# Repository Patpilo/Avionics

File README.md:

# Avionics
Avionics for Lynx Rocket

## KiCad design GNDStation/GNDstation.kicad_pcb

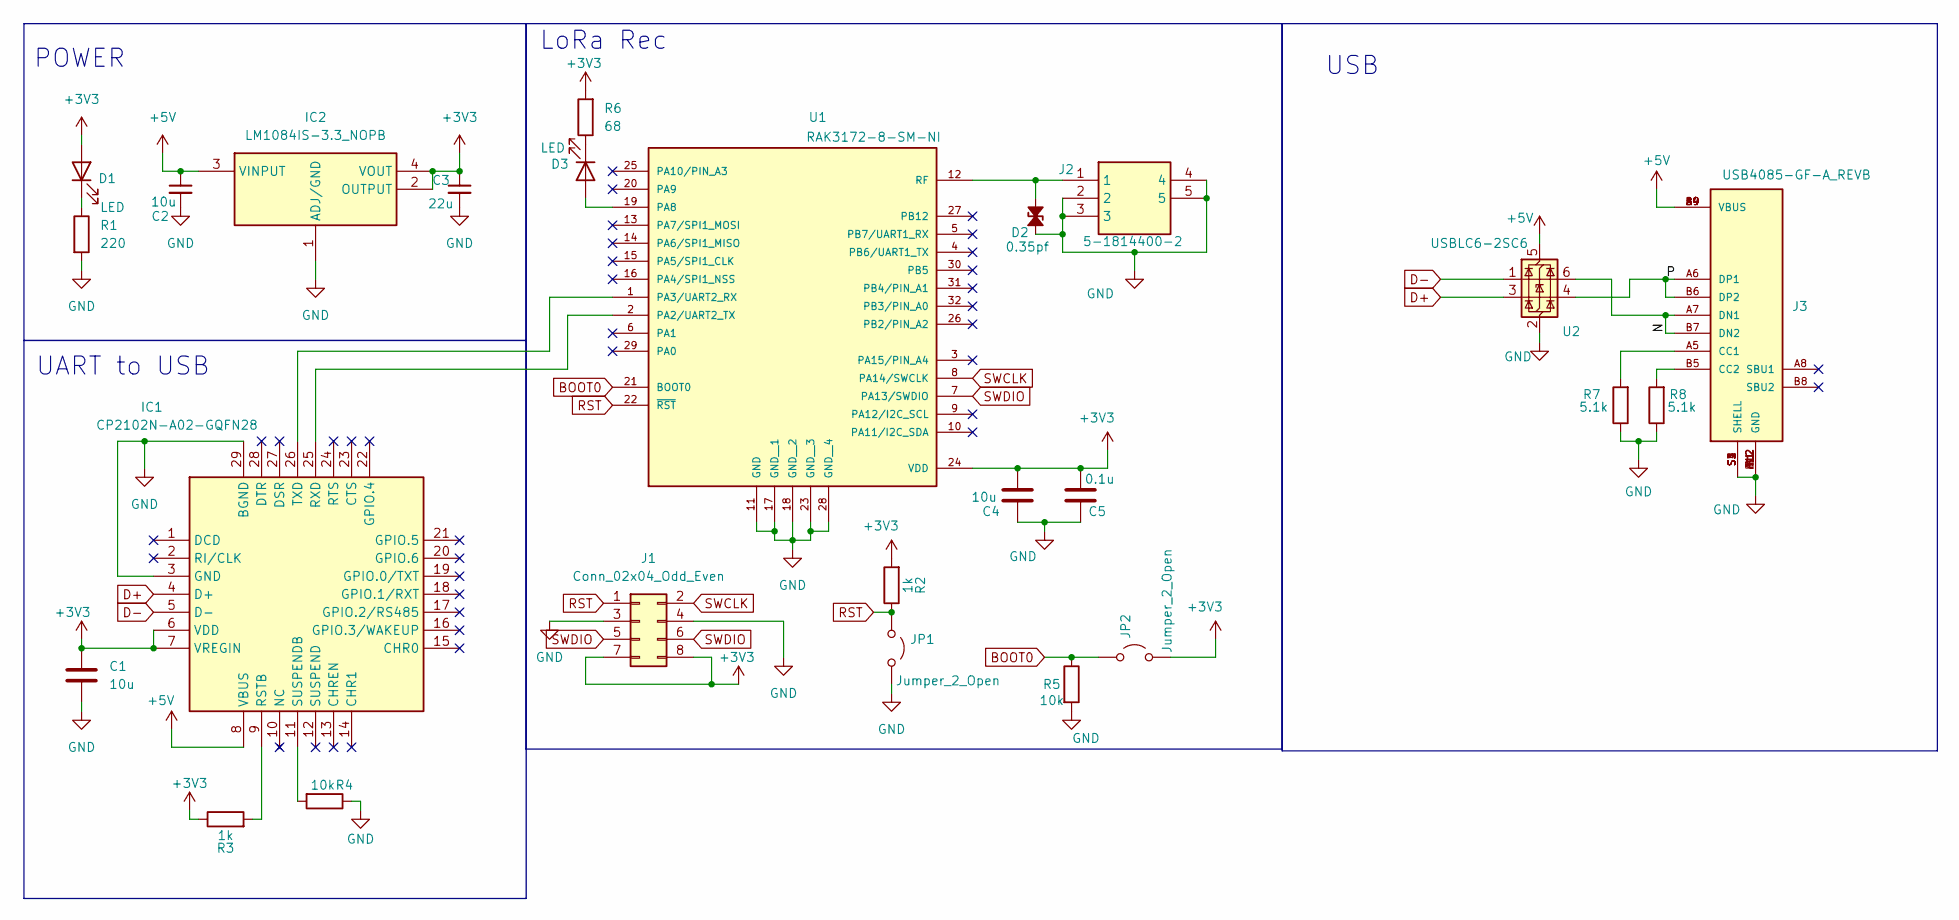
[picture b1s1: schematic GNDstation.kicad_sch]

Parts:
C1, C2, C4: 10u; C_0805_2012Metric_Pad1.18x1.45mm_HandSolder
C3: 22u; C_0805_2012Metric_Pad1.18x1.45mm_HandSolder
C5: 0.1u; C_0201_0603Metric_Pad0.64x0.40mm_HandSolder
D1, D3: LED; LED_0805_2012Metric_Pad1.15x1.40mm_HandSolder
D2: 0.35pf; D_01005_0402Metric_Pad0.57x0.30mm_HandSolder
IC1: CP2102N-A02-GQFN28; QFN50P500X500X80-29N-D; Manufacturer_Part_Number CP2102N-A02-GQFN28; Mouser Part Number 634-CP2102NA02GQFN28
IC2: LM1084IS-3.3_NOPB; TO254P1435X464-4N; Manufacturer_Part_Number LM1084IS-3.3/NOPB; Mouser Part Number 926-LM1084IS-3.3NOPB
J1: Conn_02x04_Odd_Even; PinHeader_2x04_P2.54mm_Vertical
J2: 5-1814400-2; 518144002; Manufacturer_Part_Number 5-1814400-2; Mouser Part Number 571-5-1814400-2
J3: USB4085-GF-A_REVB; GCT_USB4085-GF-A_REVB; PARTREV B
JP1, JP2: Jumper_2_Open; SolderJumper-2_P1.3mm_Open_RoundedPad1.0x1.5mm
R1: 220; R_0805_2012Metric_Pad1.20x1.40mm_HandSolder
R2, R3: 1k; R_0402_1005Metric_Pad0.72x0.64mm_HandSolder
R4, R5: 10k; R_0805_2012Metric_Pad1.20x1.40mm_HandSolder
R6: 68; R_0805_2012Metric_Pad1.20x1.40mm_HandSolder
R7, R8: 5.1k; R_0402_1005Metric_Pad0.72x0.64mm_HandSolder
U1: RAK3172-8-SM-NI; XCVR_RAK3172-8-SM-NI; PARTREV 4/11/2023
U2: USBLC6-2SC6; SOT-23-6

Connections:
+3V3: C1.1, C3.1, C4.2, C5.2, D1.2 (A), IC1.6 (VDD), IC1.7 (VREGIN), IC2.2 (OUTPUT), IC2.4 (VOUT), J1.7, J1.8, JP2.2 (B), R2.2, R3.1, R6.2, U1.24 (VDD)
+5V: C2.1, IC1.8 (VBUS), IC2.3 (VINPUT), J3.A4 (VBUS), J3.A9 (VBUS), J3.B4 (VBUS), J3.B9 (VBUS), U2.5 (VBUS)
/N: J3.A7 (DN1), J3.B7 (DN2), U2.6 (I/O1)
/P: J3.A6 (DP1), J3.B6 (DP2), U2.4 (I/O2)
BOOT0: JP2.1 (A), R5.1, U1.21 (BOOT0)
D+: IC1.4 (D+), U2.3 (I/O2)
D-: IC1.5 (D-), U2.1 (I/O1)
GND: C1.2, C2.2, C3.2, C4.1, C5.1, D2.1 (A1), IC1.3 (GND), IC1.29 (BGND), IC2.1 (ADJ/GND), J1.3, J1.4, J2.2, J2.3, J2.4, J2.5, J3.A1 (GND), J3.A12 (GND), J3.B1 (GND), J3.B12 (GND), J3.S1 (SHELL), J3.S2 (SHELL), J3.S3 (SHELL), J3.S4 (SHELL), JP1.2 (B), R1.2, R4.1, R5.2, R7.1, R8.1, U1.11 (GND), U1.17 (GND__1), U1.18 (GND__2), U1.23 (GND__3), U1.28 (GND__4), U2.2 (GND)
unnamed: D1.1 (K), R1.1
unnamed: D2.2 (A2), J2.1, U1.12 (RF)
unnamed: D3.2 (A), U1.19 (PA8)
unnamed: D3.1 (K), R6.1
unnamed: IC1.9 (RSTB), R3.2
unnamed: IC1.25 (RXD), U1.2 (PA2/UART2_TX)
unnamed: IC1.11 (SUSPENDB), R4.2
unnamed: IC1.26 (TXD), U1.1 (PA3/UART2_RX)
unnamed: J3.A5 (CC1), R7.2
unnamed: J3.B5 (CC2), R8.2
RST: J1.1, JP1.1 (A), R2.1, U1.22 (~RST)
SWCLK: J1.2, U1.8 (PA14/SWCLK)
SWDIO: J1.5, J1.6, U1.7 (PA13/SWDIO)

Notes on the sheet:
POWER
UART to USB
LoRa Rec
USB

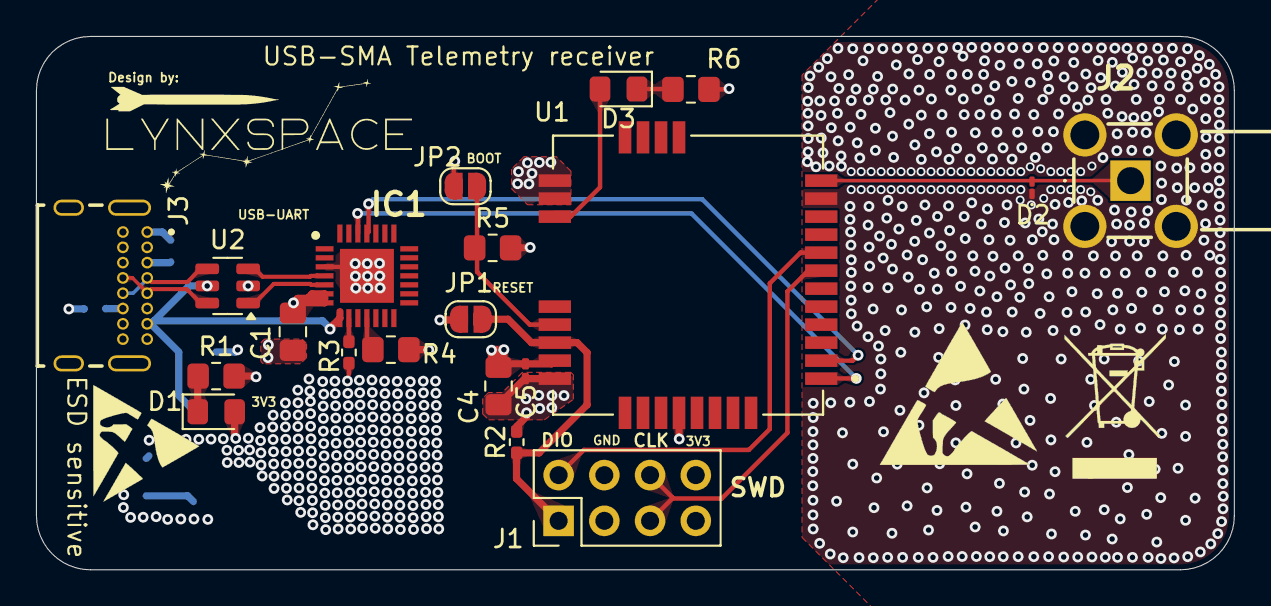
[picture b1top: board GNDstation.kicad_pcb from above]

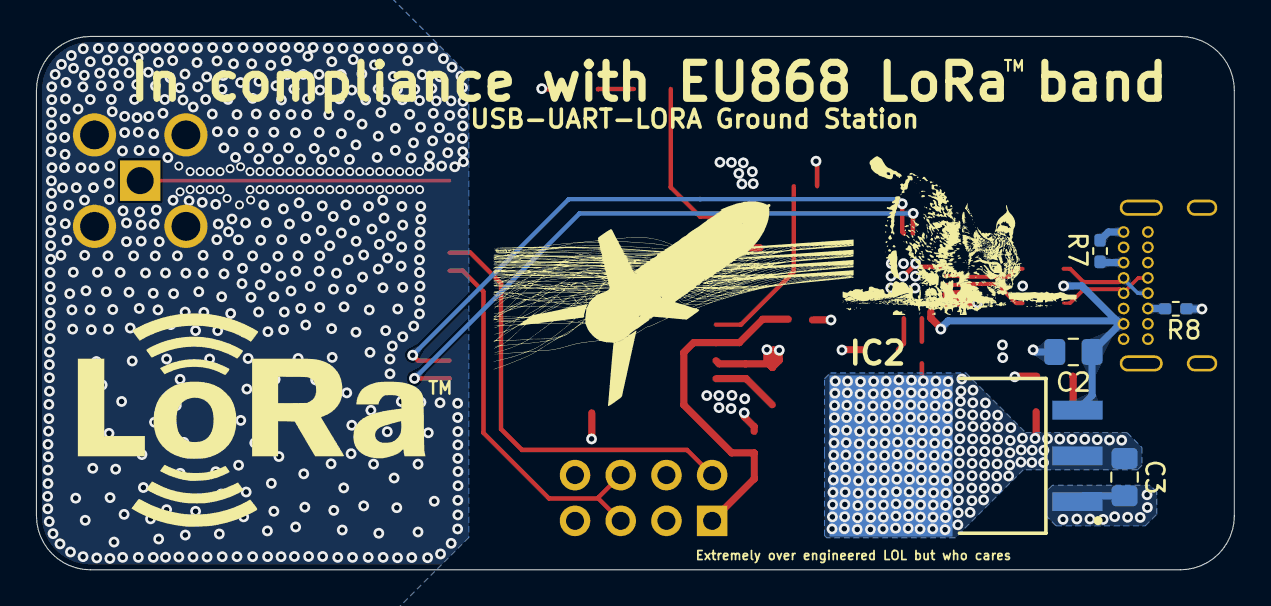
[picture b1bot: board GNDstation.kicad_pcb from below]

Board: 4 copper layers, 66.5 x 29.6 mm, 25 parts (5 on the bottom side), 21 nets.

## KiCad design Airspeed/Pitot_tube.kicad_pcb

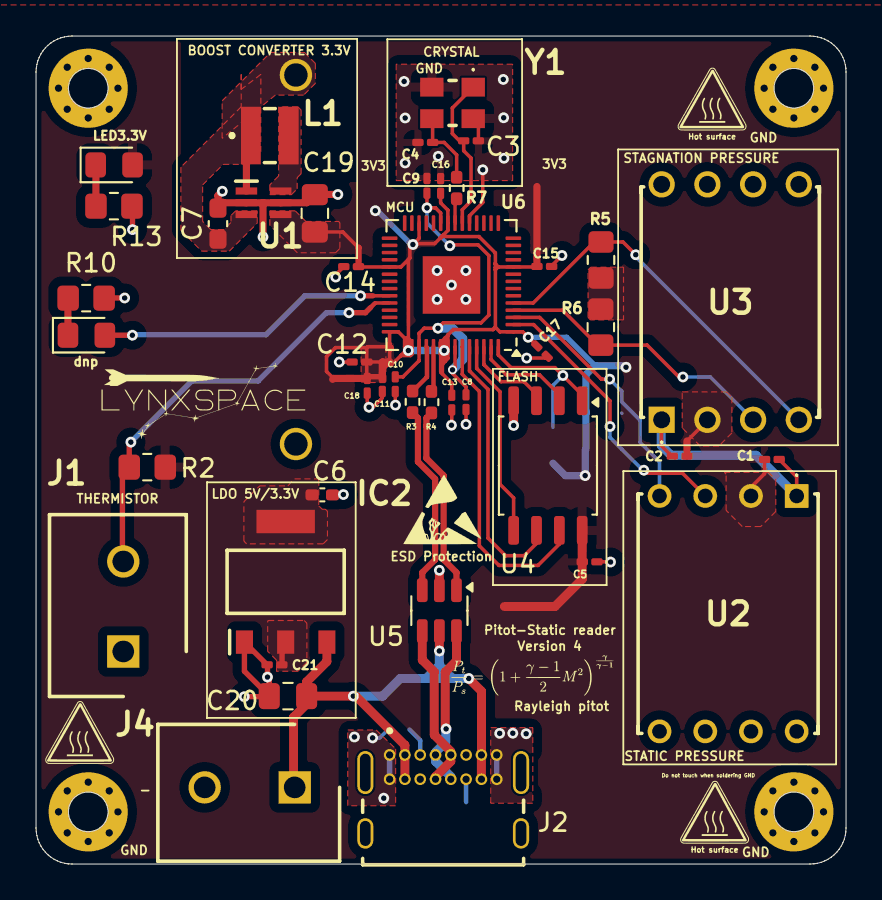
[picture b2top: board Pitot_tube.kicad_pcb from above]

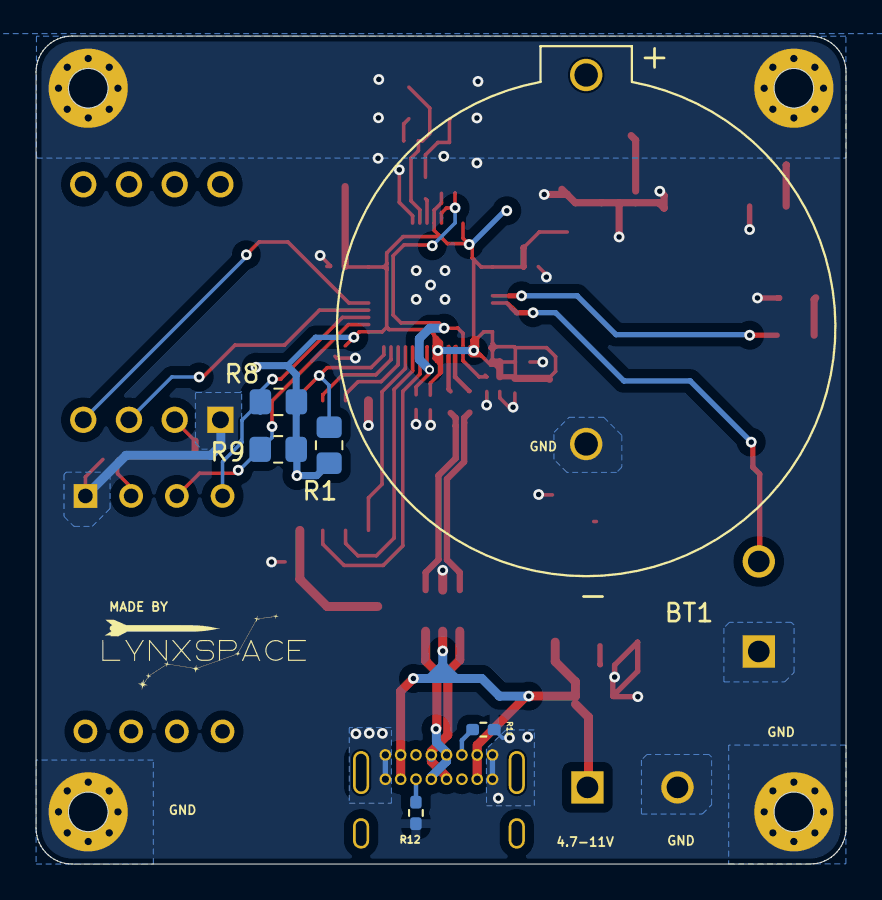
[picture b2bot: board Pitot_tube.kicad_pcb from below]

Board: 2 copper layers, 45.0 x 46.0 mm, 53 parts (6 on the bottom side), 31 nets.

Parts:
BT1: BH1000G; BAT_BH1000G
C1, C2, C21: 0.1u; C_0201_0603Metric_Pad0.64x0.40mm_HandSolder
C3, C4: 15p; C_0201_0603Metric_Pad0.64x0.40mm_HandSolder
C5, C8, C9, C12, C13, C14, C15, C16, C17, C18: 100n; C_0201_0603Metric_Pad0.64x0.40mm_HandSolder
C6: 22u; C_0402_1005Metric_Pad0.74x0.62mm_HandSolder
C7: 1u; C_0603_1608Metric_Pad1.08x0.95mm_HandSolder
C10, C11: 1u; C_0201_0603Metric_Pad0.64x0.40mm_HandSolder
C19, C20: 10u; C_0805_2012Metric_Pad1.18x1.45mm_HandSolder
D1: dnp; LED_0805_2012Metric_Pad1.15x1.40mm_HandSolder
D2: LED; LED_0805_2012Metric_Pad1.15x1.40mm_HandSolder
H1, H2, H3, H4: MountingHole_Pad_MP; MountingHole_2.2mm_M2_Pad_Via
IC2: AMS1117-3.3; SOT229P700X180-4N
J1: Screw_Terminal_01x02/Thermistor; SHDR2W70P0X500_1X2_1000X750X1160P
J2: USB4085-GF-A_REVB; GCT_USB4085-GF-A_REVB
J4: 691137710002; SHDR2W70P0X500_1X2_1000X750X1160P
L1: 10u; SRN3012TA2R2M
R1, R10: dnp; R_0805_2012Metric_Pad1.20x1.40mm_HandSolder
R2: 10k; R_0805_2012Metric_Pad1.20x1.40mm_HandSolder
R3, R4: 27.4; R_0402_1005Metric_Pad0.72x0.64mm_HandSolder
R5, R6, R8, R9: 4.7k; R_0805_2012Metric_Pad1.20x1.40mm_HandSolder
R7: 1k; R_0402_1005Metric_Pad0.72x0.64mm_HandSolder
R11, R12: 5.1k; R_0402_1005Metric_Pad0.72x0.64mm_HandSolder
R13: 110; R_0805_2012Metric_Pad1.20x1.40mm_HandSolder
U1: LTC3525D-3.3; SOT65P210X100-6N
U2: HSCDANN015PA2A3
U3: ELVH-030A-HAND-I-N2A4; ELVH030GHANDCPSA4
U4: W25Q128JVS; SOIC-8_5.23x5.23mm_P1.27mm
U5: USBLC6-2SC6; SOT-23-6
U6: RP2040; QFN-56-1EP_7x7mm_P0.4mm_EP3.2x3.2mm
Y1: ABM8-272-T3; ABM8272T3

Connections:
+1V1: C8.1, C9.1, C10.1, U6.23 (DVDD), U6.45 (VREG_VOUT), U6.50 (DVDD)
+3V3: C1.2, C2.2, C5.1, C6.1, C11.1, C12.1, C13.1, C14.1, C15.1, C16.1, C17.1, C18.1, C19.1, C21.2, D2.2 (A), IC2.2 (VOUT_1), IC2.4 (VOUT_2), R1.1, R2.2, R5.1, R6.1, R8.1, R9.1, U1.4 (VOUT), U2.2 (VSUPPLY), U3.2 (VS), U4.8 (VCC), U6.1 (IOVDD), U6.10 (IOVDD), U6.22 (IOVDD), U6.26 (RUN), U6.33 (IOVDD), U6.42 (IOVDD), U6.43 (ADC_AVDD), U6.44 (VREG_IN), U6.48 (USB_VDD), U6.49 (IOVDD)
+5V: C20.1, IC2.3 (VIN), J2.A4 (VBUS), J2.A9 (VBUS), J2.B4 (VBUS), J2.B9 (VBUS), J4.1 (+), U5.5 (VBUS)
/SW: L1.2, U1.6 (SW)
/USB_DN: R3.2, U6.46 (USB_DM)
/USB_DP: R4.2, U6.47 (USB_DP)
D+: R4.1, U5.1 (I/O1)
D-: R3.1, U5.3 (I/O2)
FLASH_CLK: U4.6 (CLK), U6.52 (QSPI_SCLK)
FLASH_CS: R1.2, U4.1 (~CS), U6.56 (QSPI_SS)
GND: BT1.N, C1.1, C2.1, C3.1, C4.1, C5.2, C6.2, C7.2, C8.2, C9.2, C10.2, C11.2, C12.2, C13.2, C14.2, C15.2, C16.2, C17.2, C18.2, C19.2, C20.2, C21.1, H1.1 (MP), H2.1 (MP), H3.1 (MP), H4.1 (MP), IC2.1 (GND), J1.1, J2.A1 (GND), J2.A12 (GND), J2.B1 (GND), J2.B12 (GND), J4.2 (-), R10.1, R11.1, R12.1, R13.2, U1.2 (GND), U1.5 (GND), U2.1 (GND), U3.1 (GND), U4.4 (GND), U5.2 (GND), U6.19 (TESTEN), U6.57 (GND), Y1.2, Y1.4
GPIO_ADC_THERM: J1.2, R2.1, U6.38 (GPIO26_ADC0)
unnamed: C4.2, R7.1, Y1.3
unnamed: D1.2 (A), U6.37 (GPIO25)
unnamed: D1.1 (K), R10.2
unnamed: D2.1 (K), R13.1
unnamed: J2.A5 (CC1), R11.2
unnamed: J2.B5 (CC2), R12.2
QSPI_SD0: U4.5 (DI(IO0)), U6.53 (QSPI_SD0)
QSPI_SD1: U4.2 (DO(IO1)), U6.55 (QSPI_SD1)
QSPI_SD2: U4.3 (IO2), U6.54 (QSPI_SD2)
QSPI_SD3: U4.7 (IO3), U6.51 (QSPI_SD3)
SENS_SCL0: R8.2, U2.4 (SCL), U6.3 (GPIO1)
SENS_SCL1: R5.2, U3.4 (SCLK), U6.5 (GPIO3)
SENS_SDA0: R9.2, U2.3 (SDA), U6.2 (GPIO0)
SENS_SDA1: R6.2, U3.3 (MISO), U6.4 (GPIO2)
VCC: BT1.P, C7.1, L1.1, U1.1 (~SHDN), U1.3 (VIN)
XIN: C3.2, U6.20 (XIN), Y1.1
XOUT: R7.2, U6.21 (XOUT)
connD+: J2.A6 (DP1), J2.B6 (DP2), U5.6 (I/O1)
connD-: J2.A7 (DN1), J2.B7 (DN2), U5.4 (I/O2)

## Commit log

2025-08-07 Create LynxYNav
2025-08-07 Create Main
